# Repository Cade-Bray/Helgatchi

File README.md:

# Helgatchi
Handheld BLE + WiFi Hunter

## What is it?
A portable, hand-held BLE beacon and WiFi AP scanner/hunter, with built-in alerting, 1.69” full-color screen, and external SMA-RP antenna all powered by the XIAO ESP32-S3. 

The Helgatchi will passively scan for BLE devices and WiFi SSIDs/APs, and alert when specific Manufacturers, naming schemes, or services are discovered. 

It can be configured to alert anything you want, such as:
- Flock technology
- AXON technology
- Wearable health devices
- Any specific device
- Hidden WiFi/Bluetooth cameras

## Key Features
- Enclosed, portable, battery powered handheld rechargeable BLE and WiFi scanner and hunter that can live in your pocket.
- Passively scans for beacons in the background in-between sleeping, and actively scans when an alert is triggered.
- Powered by the XIAO ESP32-S3
- 6 RGB LEDs
- 1.69" rounded screen
- Vibration motor for alerts
- You can change
  - Color scheme
  - Alert settings
    - Vibrate
    - LEDs
    - Screen Wake
  - Scan settings
    - Sleep duration
    - Scan duration
  - Rules for alerts
    - MAC address (BLE, WiFi)
    - Manufacturer (BLE, WiFi OUI)
    - Device name (BLE name, WiFi SSID)
    - Service (BLE)

## Specifications

| Spec      | Info                                             	|
|----------	|---------------------------------------------------	|
| MCU      	| XIAO ESP32-S3                                     	|
| Flash    	| 8MB                                               	|
| Battery  	| 800mAh - 1200mAh 3.7v LiPo                        	|
| Screen   	| Waveshare 1.69” LCD - 240p × 280p                 	|
| Firmware 	| platform.io + Arduino                             	|
| Software 	| Graphics: LVGL BLE: NimBLE LEDs: FastLED          	|
| Antenna  	| XIAO -> u.FL > back PCB > SMA-RP > 2.4Ghz antenna 	|
| Size     	| Width: 50mm Length: 80mm Height: TBD              	|

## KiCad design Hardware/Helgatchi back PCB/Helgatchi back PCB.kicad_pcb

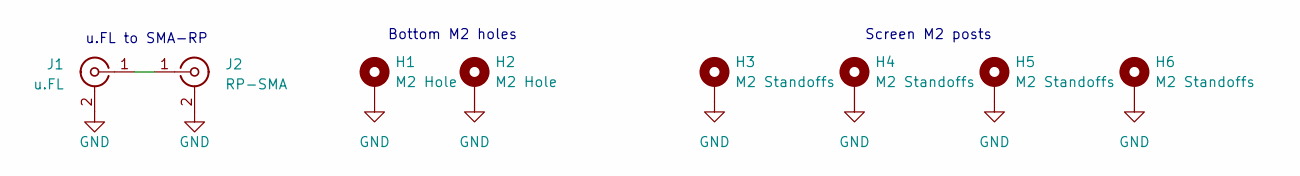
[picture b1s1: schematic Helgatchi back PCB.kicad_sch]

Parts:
H1, H2: M2 Hole; MountingHole_2.2mm_M2_Pad_Via
H3, H4, H5, H6: M2 Standoffs; MountingHole_2.2mm_M2_Pad_Via; LCSC Part # C2928171
J1: u.FL; U.FL_Molex_MCRF_73412-0110_Vertical; LCSC Part # C411563
J2: RP-SMA; SMA_Amphenol_901-143_Horizontal; LCSC Part # C1509217

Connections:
GND: H1.1, H2.1, H3.1, H4.1, H5.1, H6.1, J1.2 (Ext), J2.2 (Ext)
unnamed: J1.1 (In), J2.1 (In)

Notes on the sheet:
Bottom M2 holes
Screen M2 posts
u.FL to SMA-RP

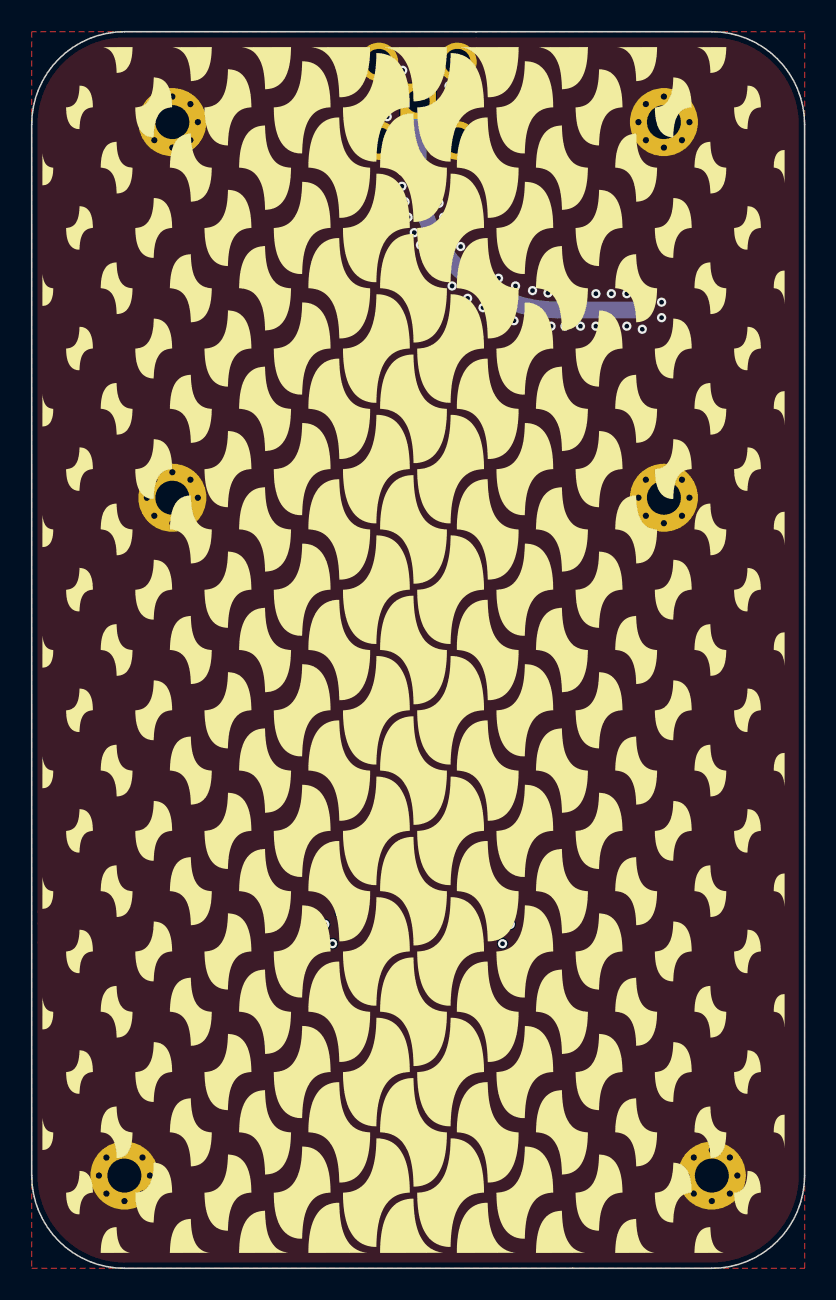
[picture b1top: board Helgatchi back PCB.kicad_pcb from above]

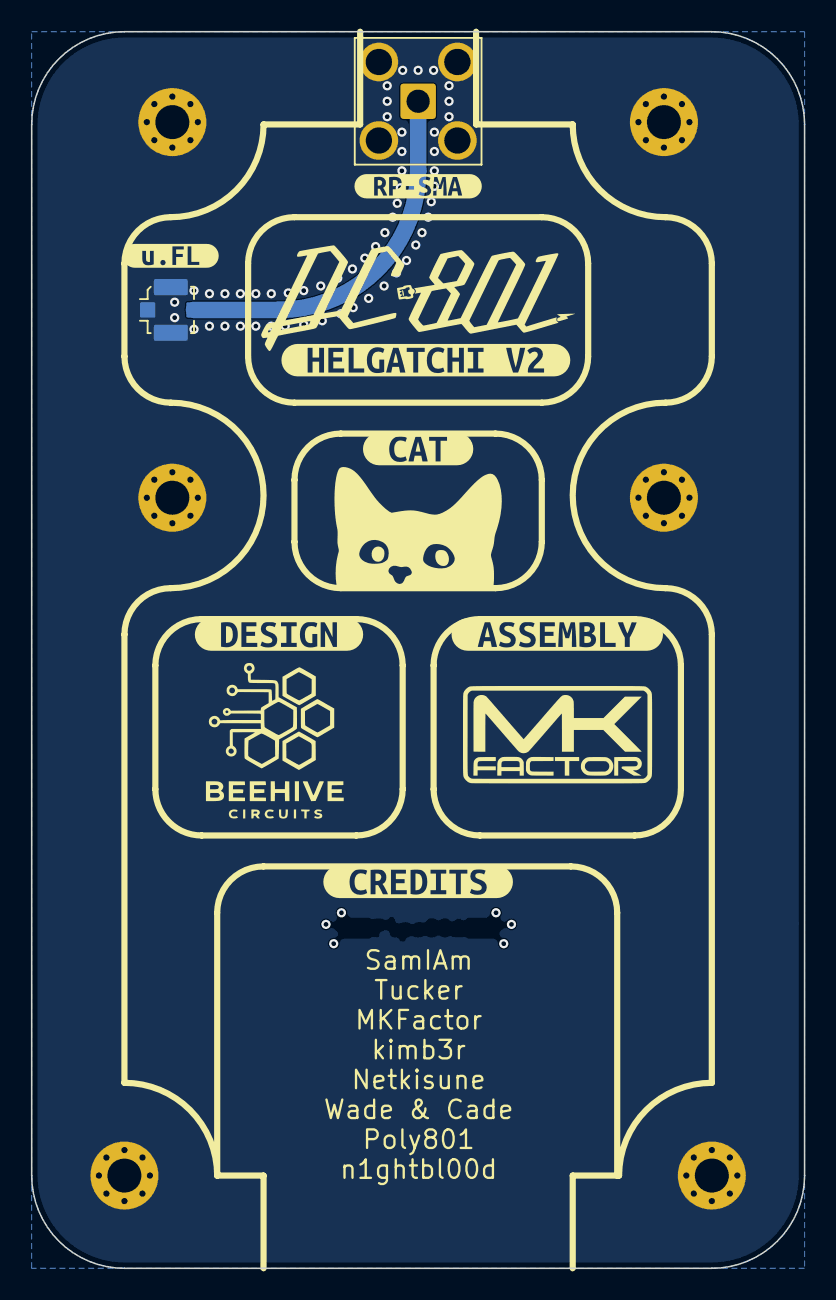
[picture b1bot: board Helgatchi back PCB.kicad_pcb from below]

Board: 2 copper layers, 50.0 x 80.0 mm, 15 parts (13 on the bottom side), 2 nets.

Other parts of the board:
kibuzzard-69B731C5: G***; kibuzzard-69B731C5
kibuzzard-69B731D4: G***; kibuzzard-69B731D4
kibuzzard-69B735E8: G***; kibuzzard-69B735E8
kibuzzard-69B7363E: G***; kibuzzard-69B7363E
kibuzzard-69B73206: G***; kibuzzard-69B73206
kibuzzard-69B73420: G***; kibuzzard-69B73420
kibuzzard-69B73430: G***; kibuzzard-69B73430

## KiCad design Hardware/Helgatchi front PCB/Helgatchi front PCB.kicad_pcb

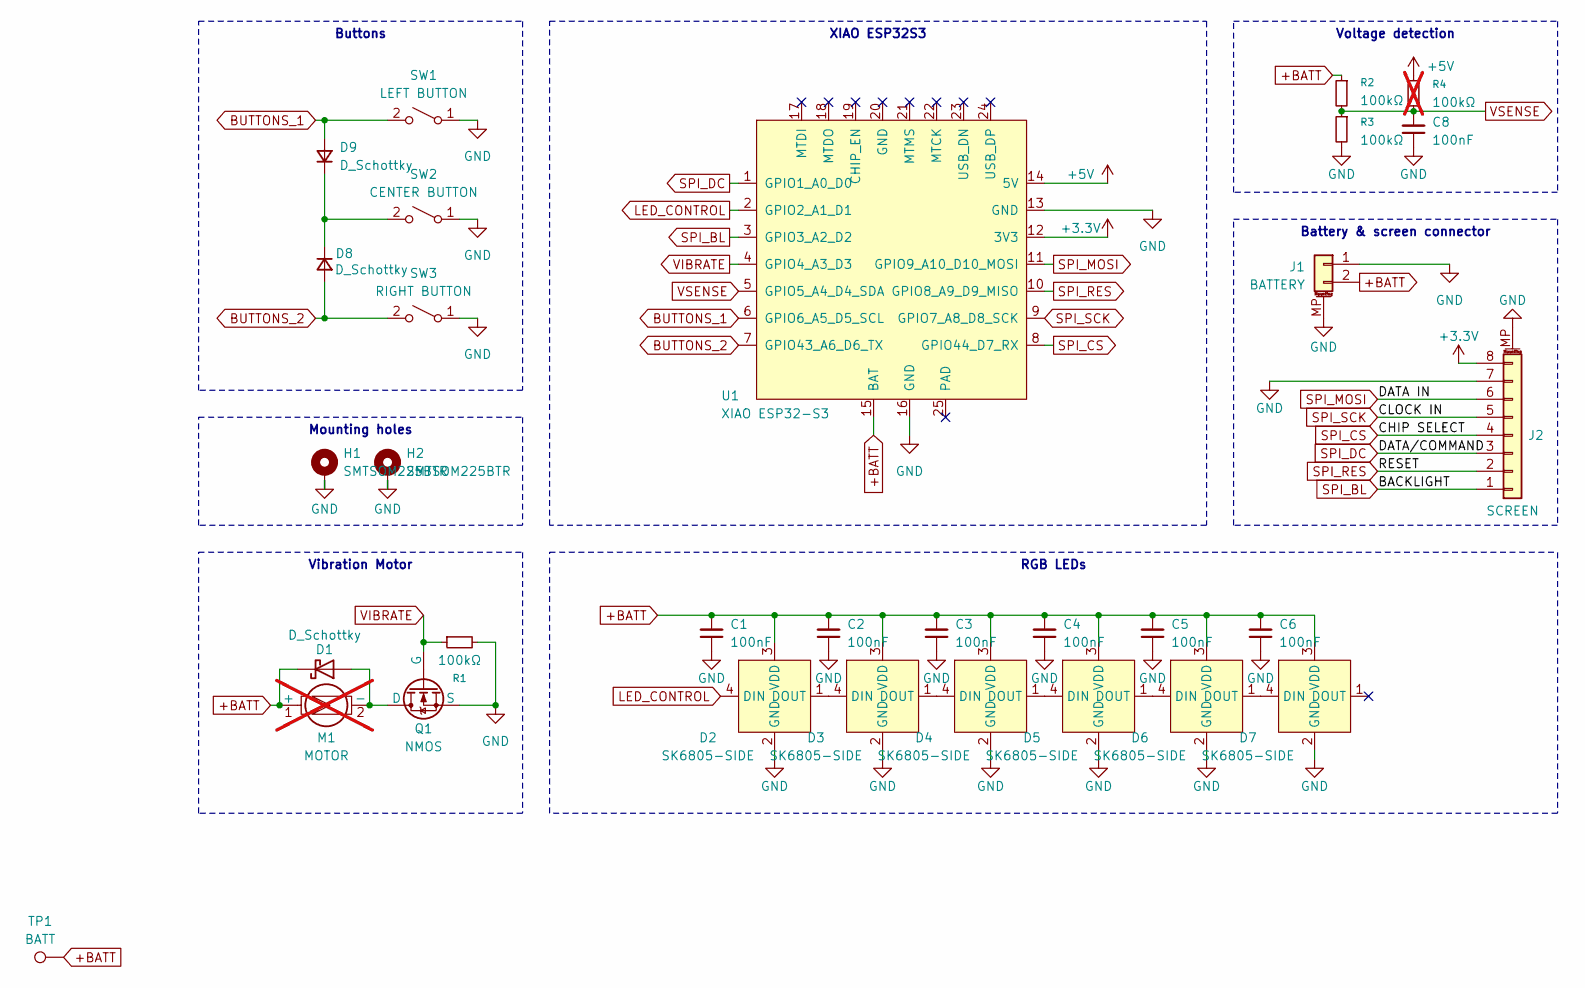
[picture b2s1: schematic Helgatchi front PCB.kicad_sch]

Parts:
C1, C2, C3, C4, C5, C6, C8: 100nF; C_0603_1608Metric; LCSC Part # C14663
D1, D8, D9: D_Schottky; D_SOD-523; LCSC Part # C7420320
D2, D3, D4, D5, D6, D7: SK6805-SIDE; LED-SMD_4P-L3.5-W1.6_SK6805SIDE-G-001; MPN SK6805SIDE-G-003; LCSC Part # C42417604
H1, H2: SMTSOM225BTR; SMD_BD5.6-D3.6; LCSC Part # C5301773
J1: BATTERY; JST_SH_SM02B-SRSS-TB_1x02-1MP_P1.00mm_Horizontal; LCSC Part # C160402
J2: SCREEN; Molex_PicoBlade_53261-0871_1x08-1MP_P1.25mm_Horizontal; LCSC Part # C7433459
M1: MOTOR; PinHeader_1x02_P2.54mm_Vertical; LCSC Part # C2682302; not fitted
Q1: NMOS; SOT-23; LCSC Part # C20917
R1, R2, R3: 100kΩ; R_0603_1608Metric; LCSC Part # C25803
R4: 100kΩ; R_0603_1608Metric; LCSC Part # C25803; not fitted
SW1: LEFT BUTTON; Reverse button footprint; LCSC Part # C9900250000
SW2: CENTER BUTTON; Reverse button footprint; LCSC Part # C9900250000
SW3: RIGHT BUTTON; Reverse button footprint; LCSC Part # C9900250000
TP1: BATT; TestPoint_Pad_D1.0mm
U1: XIAO ESP32-S3; XIAO-ESP32S3-SMD; LCSC Part # C9900124959

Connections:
+3.3V: J2.8, U1.12 (3V3)
+5V: R4.1, U1.14 (5V)
+BATT: C1.2, C2.2, C3.2, C4.2, C5.2, C6.2, D1.1 (K), D2.3 (VDD), D3.3 (VDD), D4.3 (VDD), D5.3 (VDD), D6.3 (VDD), D7.3 (VDD), J1.2, M1.1 (+), R2.1, TP1.1 (1_1), U1.15 (BAT)
BUTTONS_1: D9.2 (A), SW1.2 (B), U1.6 (GPIO6_A5_D5_SCL)
BUTTONS_2: D8.2 (A), SW3.2 (B), U1.7 (GPIO43_A6_D6_TX)
GND: C1.1, C2.1, C3.1, C4.1, C5.1, C6.1, C8.1, D2.2 (GND), D3.2 (GND), D4.2 (GND), D5.2 (GND), D6.2 (GND), D7.2 (GND), H1.1 (1_1), H2.1 (1_1), J1.1, J1.MP (MountPin), J2.7, J2.MP (MountPin), Q1.2 (S), R1.2, R3.2, SW1.1 (A), SW2.1 (A), SW3.1 (A), U1.13 (GND), U1.16 (GND)
LED_CONTROL: D2.4 (DIN), U1.2 (GPIO2_A1_D1)
unnamed: D1.2 (A), M1.2 (-), Q1.3 (D)
unnamed: D2.1 (DOUT), D3.4 (DIN)
unnamed: D3.1 (DOUT), D4.4 (DIN)
unnamed: D4.1 (DOUT), D5.4 (DIN)
unnamed: D5.1 (DOUT), D6.4 (DIN)
unnamed: D6.1 (DOUT), D7.4 (DIN)
unnamed: D8.1 (K), D9.1 (K), SW2.2 (B)
SPI_BL: J2.1, U1.3 (GPIO3_A2_D2)
SPI_CS: J2.4, U1.8 (GPIO44_D7_RX)
SPI_DC: J2.3, U1.1 (GPIO1_A0_D0)
SPI_MOSI: J2.6, U1.11 (GPIO9_A10_D10_MOSI)
SPI_RES: J2.2, U1.10 (GPIO8_A9_D9_MISO)
SPI_SCK: J2.5, U1.9 (GPIO7_A8_D8_SCK)
VIBRATE: Q1.1 (G), R1.1, U1.4 (GPIO4_A3_D3)
VSENSE: C8.2, R2.2, R3.1, R4.2, U1.5 (GPIO5_A4_D4_SDA)

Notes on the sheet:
XIAO ESP32S3
Buttons
RGB LEDs
Voltage detection
Vibration Motor
Battery & screen connector
Mounting holes

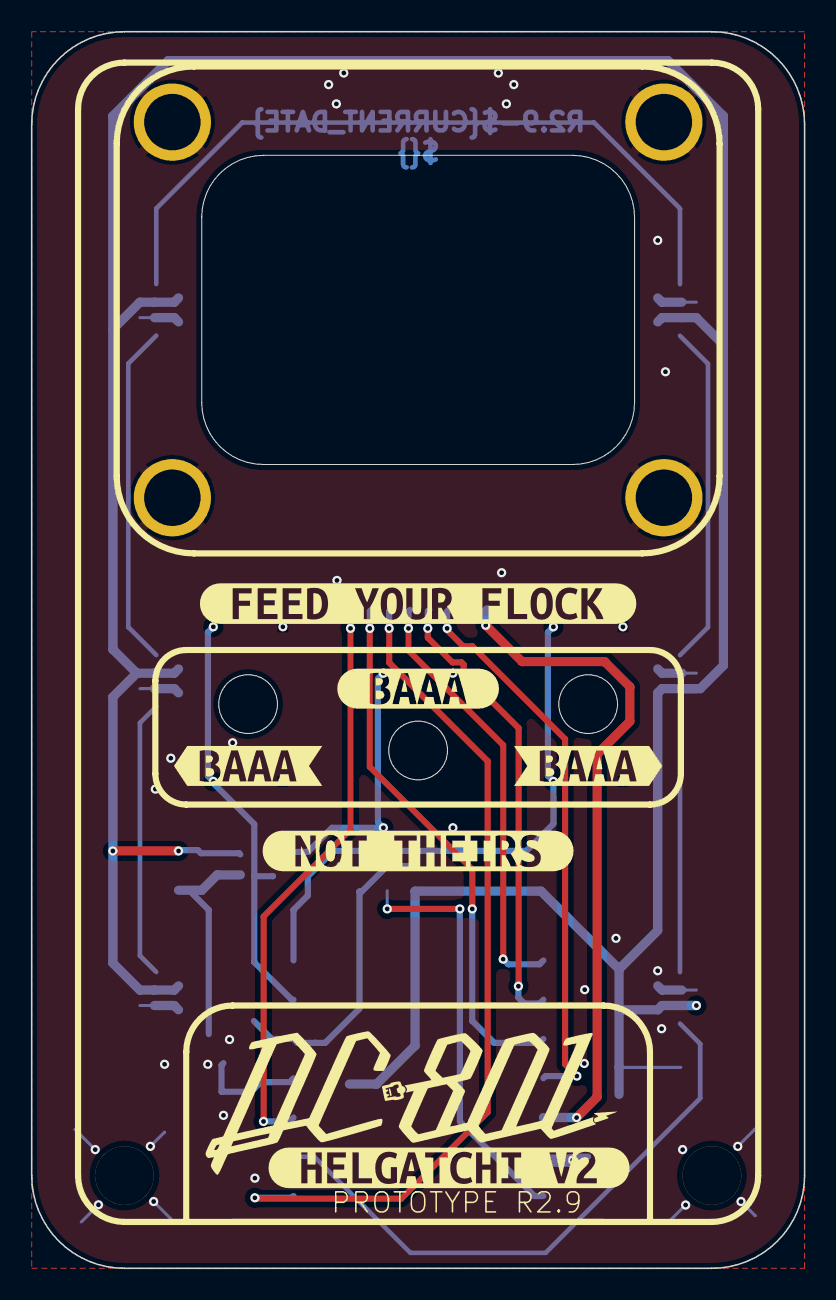
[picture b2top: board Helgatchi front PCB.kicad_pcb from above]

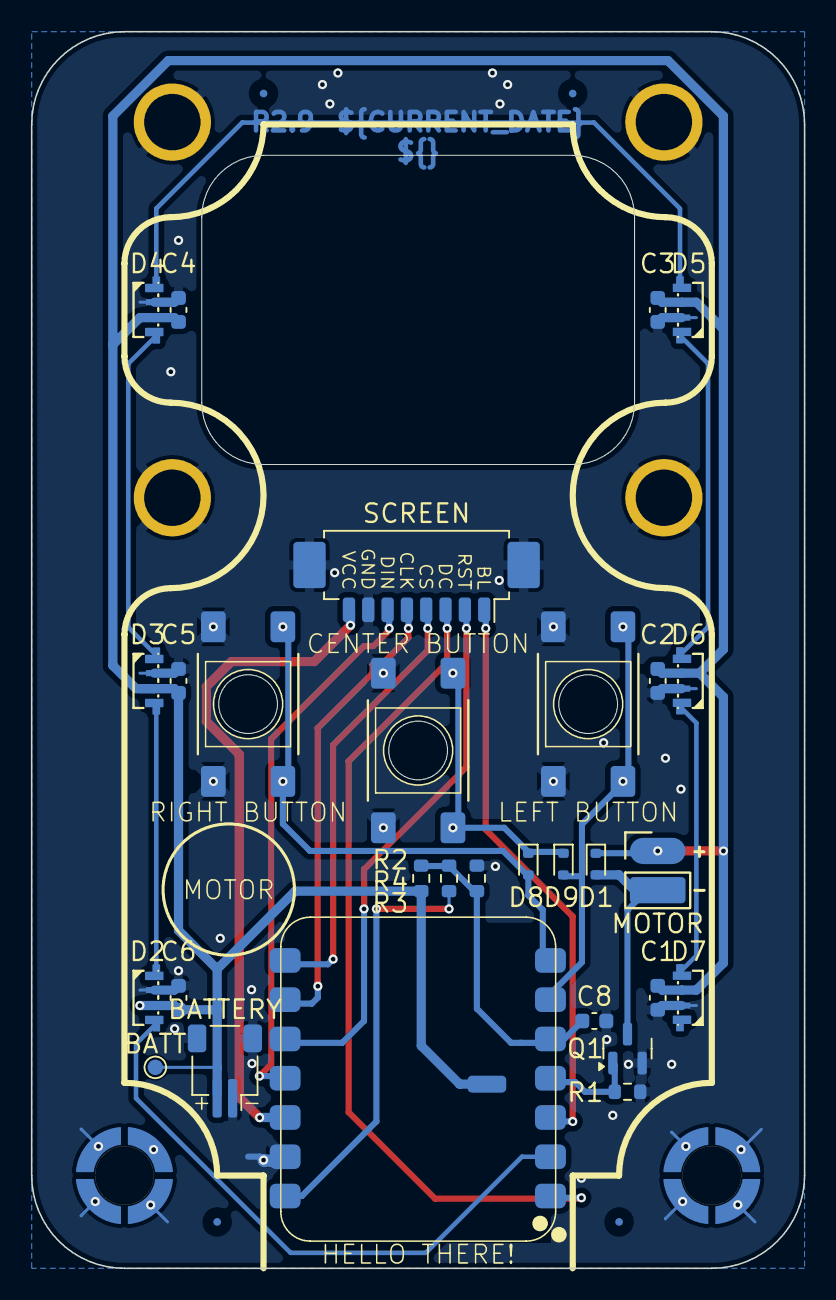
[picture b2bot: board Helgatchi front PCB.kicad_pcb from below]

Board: 2 copper layers, 50.0 x 80.0 mm, 38 parts (31 on the bottom side), 22 nets.

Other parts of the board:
Untitled: Waveshare 1.69"; Waveshare 1.69_
kibuzzard-6976EA3A: G***; kibuzzard-6976EA3A
kibuzzard-6976EA47: G***; kibuzzard-6976EA47
kibuzzard-6976EDA9: G***; kibuzzard-6976EDA9
kibuzzard-6976EEFC: G***; kibuzzard-6976EEFC
kibuzzard-6976EF0C: G***; kibuzzard-6976EF0C
kibuzzard-69862DFC: G***; kibuzzard-69862DFC

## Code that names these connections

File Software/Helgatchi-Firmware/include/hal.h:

#pragma once
#include "lgfx_config.h"
#include <FastLED.h>
#include "event_bus.h"
#include <esp_timer.h>

// ---------------------------------------------------------------------------
// GPIO pin assignments (from GPIO.md)
// NOTE: GPIO43 is ESP32-S3 UART0 TX. On XIAO ESP32-S3, Serial = USB CDC,
//       so UART0 is unused and GPIO43 is free for button input.
// ---------------------------------------------------------------------------
static constexpr uint8_t PIN_SPI_DC   =  1;
static constexpr uint8_t PIN_LED_DATA =  2;
static constexpr uint8_t PIN_SPI_BL   =  3;  // backlight — PWM controlled by HAL
static constexpr uint8_t PIN_VIBRATE  =  4;
static constexpr uint8_t PIN_VSENSE   =  5;
static constexpr uint8_t PIN_BTN_1    =  6;  // button matrix line A
static constexpr uint8_t PIN_BTN_2    = 43;  // button matrix line B
static constexpr uint8_t PIN_SPI_CS   = 44;
static constexpr uint8_t PIN_SPI_SCK  =  7;
static constexpr uint8_t PIN_SPI_RST  =  8;
static constexpr uint8_t PIN_SPI_MOSI =  9;

// ---------------------------------------------------------------------------
// HAL tuning constants
// ---------------------------------------------------------------------------
static constexpr uint8_t  HAL_NUM_LEDS       =  6;
static constexpr uint16_t HAL_LONG_PRESS_MS  =  600;
static constexpr uint16_t HAL_HOLD_MS        = 2500;   // center-hold-to-sleep (wake holds live in power_manager)
static constexpr uint8_t  HAL_DEBOUNCE_MS    =   20;
static constexpr uint8_t  HAL_BTN_POLL_MS    =    5;   // fixed button sample rate (esp_timer), decoupled from loop cadence
static constexpr uint8_t  HAL_BL_LEDC_CH     =  0;   // LEDC channel for backlight PWM
static constexpr uint8_t  HAL_VIBE_LEDC_CH   =  1;   // LEDC channel for vibration motor PWM

// Backlight PWM levels mapped to ScreenBrightness enum indices
//                                            MIN  LOW  MED  HIGH  MAX
static constexpr uint8_t HAL_BL_LEVELS[]  = {  15,  50, 110,  180, 255 };
// LED global brightness levels mapped to LEDBrightness enum indices
static constexpr uint8_t HAL_LED_LEVELS[] = {  20,  60, 130,  255 };

// ---------------------------------------------------------------------------

class HAL : public IEventHandler {
public:
    // Initialise all peripherals and subscribe to relevant bus events.
    void begin(EventBus& bus);

    // Service the USB-attach (SOF) detector. Call every loop(). Button polling
    // runs on its own esp_timer (see _btnTimerCb) so input sampling isn't
    // coupled to loop/render cadence; tick() only falls back to polling if that
    // timer failed to create.
    void tick();

    // --- LEDs (call showLEDs() is implicit on each set call) ---
    void setLED(uint8_t idx, uint8_t r, uint8_t g, uint8_t b);
    void setAllLEDs(uint8_t r, uint8_t g, uint8_t b);
    void clearLEDs();

    // Push a full N-LED frame in one FastLED.show() call. Used by LedService
    // for animated patterns where we'd otherwise pay N show()s per frame.
    void writeLEDFrame(const CRGB frame[HAL_NUM_LEDS]);

    // --- Vibration (PWM-driven, 0–255 duty) ---
    // Raw level control. VibeService owns timing + patterns; callers that want
    // simple feedback should go through it instead of poking these directly.
    void setVibrate(uint8_t intensity);
    void stopVibrate();

    // --- Display ---
    LGFX& tft()                          { return _tft; }
    void  setBacklight(uint8_t val);  // 0–255

    // Display state transitions, all driven by PowerManager. begin() leaves the
    // screen OFF — wake/dim/sleepDisplay actually drive the backlight. The
    // dim/sleep variants are transient (still in interactive use): for deep
    // sleep entry call prepareForSleep() instead.
    void  wakeDisplay();    // BL → user's stored brightness
    void  dimDisplay();     // BL → MIN level (last 5 s before sleep)
    void  sleepDisplay();   // BL → 0 (silent scan window, no user-visible UI)

    // Call right before esp_deep_sleep_start(). Detaches LEDC from the
    // backlight pin, drives it LOW, and locks the pad state through deep
    // sleep — without this, the LEDC peripheral powers down during sleep
    // and the backlight reverts on, leaving the last frame visibly burnt-in.
    void  prepareForSleep();

    // Turn peripherals (motor / LEDs / backlight) off ahead of a software
    // reset (ESP.restart). Unlike prepareForSleep it doesn't hold pads or
    // sleep the panel — the reboot re-inits them. Prevents LEDC from holding
    // its last PWM duty (motor / backlight) across the reset until begin()
    // re-inits it, which is what left the motor buzzing through a reboot.
    void  prepareForReboot();

    // --- Power sensing ---
    // Returns raw voltage at the VSENSE ADC pin in millivolts (VBATT/2 divider).
    uint16_t readVsenseMv();

    // Returns true if USB is physically attached.
    // Updated non-blocking every 2 ms in tick() via SOF frame detection.
    // Does NOT detect wall chargers (no SOF packets from dumb chargers).
    bool usbAttached() const { return _usb_attached; }

    // IEventHandler — reacts to EV_SETTINGS_CHANGED (brightness) and
    // EV_ALERT_RAISED (buzz if vibration enabled).
    void onEvent(const Event& e) override;

private:
    void _initDisplay();
    void _initLEDs();
    void _pollButtons();
    static void _btnTimerCb(void* arg);   // esp_timer trampoline → _pollButtons()
    void _applyBrightnessSettings();

    struct BtnDebounce {
        bool     state        = false;
        bool     raw_prev     = false;
        uint32_t stable_since = 0;
    };

    BtnDebounce _btn[3];          // [0]=Left  [1]=Right  [2]=Center
    uint32_t    _center_down_at    = 0;
    bool        _center_long_fired = false;
    bool        _center_hold_fired = false;
    esp_timer_handle_t _btn_timer  = nullptr;   // periodic button-poll timer (HAL_BTN_POLL_MS)

    bool     _usb_attached      = false;
    uint32_t _last_sof          = 0;
    uint32_t _last_sof_check_ms = 0;

    LGFX      _tft;
    CRGB      _leds[HAL_NUM_LEDS];
    EventBus* _bus = nullptr;
};

extern HAL g_hal;

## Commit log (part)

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2026-01-23 more of initial commit
2026-01-30 slopsoftware
2026-01-30 Add LVGL Helgatchi project and update Core UI BLE handling
    Introduces the new 'LVGL Helgatchi' PlatformIO project with initial structure, configuration, and example code. Updates 'Helgatchi Core' to refine BLE manufacturer name handling in the UI, adds LVGL 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
2026-02-01 Add architecture documentation for firmware design
    This document outlines the event/service architecture for the device firmware, detailing core services, public mesh behavior, and UI integration. It includes core concepts such as the Event Bus, Mess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
2026-02-01 Add SCREENS.md documentation for UI/UX architecture
    This document outlines the UI/UX screens, user interactions, and their mapping to the event/service architecture for the LVGL Helgatchi project. It includes details on UI architecture rules, screen p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
2026-02-01 LVGL built code
2026-02-05 Drawings and laser cutter files
2026-02-05 Symbols and LEDs
2026-02-05 Swap to WS2812B-4020-H2 Footprint variant
2026-02-05 Spacer changes
2026-02-06 Back PCB changes
2026-02-06 Production files
2026-02-06 backups
2026-02-06 LCSC part # changes
    - Changed MOLEX Picoblate part number out for generic picoblade
    - Added part number and adjusted DNP for ESP32-S3
2026-02-06 Silkscreen Adjustments
2026-02-06 Add fab polarity markings for diode
2026-02-06 Add SDM2U30CSP Diode footprint and swap on board
2026-02-06 R2.3
    updated version to cut through solder mask.
2026-02-06 Swap <baaa> for (baaa)
2026-02-06 Add via in pads for buttons
2026-02-07 Update architecture document header
    Removed versioning from the architecture header.
2026-02-11 Helgatchi front PCB: update to R2.5
    Bump PCB revision to R2.5 and apply small layout/text tweaks: adjust gr_text position, update render_cache label/date, add font thickness to silkscreen effects, and shift numerous silkscreen/graphics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
2026-02-11 Bump Helgatchi front PCB to R2.6
    Update KiCad board revision to R2.6 and apply minor footprint/silkscreen geometry adjustments (including PROTOTYPE silkscreen and render_cache updates dated 2026-02-11). Add production archives and b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
2026-03-15 R2.7
    - Shifted buttons up a tiny bit
    - Made room for the vibration motor to be adhered to the PCB
    - Enlarged vibration motor pads for easier hand soldering
    - Removed LED voltage selector (now 3.3v)
    - Removed unused pins from schematic and ESP32 footprint
    - Added a keepout area under ESP32
2026-03-15 Initialize README with product details for Helgatchi
    Added detailed product description, key features, and specifications for Helgatchi.
2026-03-15 Update README with project introduction
    Added a brief introduction to the Helgatchi project.
2026-03-17 Update helgatchi spacer
2026-03-24 Wrap up R2.7
    - Added voltage sensing
    - made room for Vibration buzzer
    - added SMD M2 nut
    - swapped flyback diode
2026-04-04 Front PCB drawings
2026-04-04 Spacers
2026-04-04 Front PCB r2.7 order
2026-04-04 Back PCB order
2026-04-04 Silkscreen pdf
2026-04-04 new spacers
2026-04-09 spacer updates
2026-04-09 update for screen post cutouts
2026-04-09 Variable-defined spacer
2026-04-09 Spreadsheet-defined spacer
2026-04-09 bambu slicer stuff added
2026-04-13 Start of R2.8
    - Moving to SK6805s for LEDs
    - imported footprint, symbol, and 3D model for SK6805-SIDE
    - updated footprints and symbols for LEDs
    - repositioned LEDs and capacitors
    - Swapped LED chain direction to accommodate easier routing with new pinout
2026-04-30 Wrap up R2.8
    Boards ordered, version locked
2026-05-05 Add GPIO assignments documentation
    Document GPIO assignments and their functions.
2026-06-04 Commit new UI files
2026-06-04 Add Devices screen
2026-06-04 UI work
2026-06-04 UI code files
2026-06-04 Alerts and devices work
2026-06-24 final R2.9 revision, boards ordered
2026-06-29 Update to new firmware
2026-06-29 All screens rendering
2026-06-29 All UI elements work and are tested
2026-06-29 version tracking, bump firmware version to 1.1
2026-06-29 Better storage and memory management
2026-06-29 UI fixes and performance
2026-06-29 Moved LVGL memory heap to PSRAM
2026-06-29 More performance upgrades
2026-06-30 Alert page wired up, alert service created, serial commands added
2026-06-30 rules engine
2026-06-30 fix screen sleep issue
2026-06-30 stop suppression
2026-06-30 claude info
2026-06-30 Bug fixes
2026-06-30 Add Focus on Alerts page setting to UI
2026-06-30 Add focus on alerts page behavior
2026-06-30 scanning and behavior
